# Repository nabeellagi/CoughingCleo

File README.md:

<div align="center">

# **COUGHING CLEO**

Poor air quality monitor.

*If air == bad -> cough!*

</div>

---

# SECTIONS

- [What is Coughing Cleo](#what-is-coughing-cleo)
    - [What are Cleo's expression?](#what-are-cleos-expression)
- [Why Cleo?](#why-cleo)
- [How to use it?](#how-to-use-it)
- [What Does This Repository Include?](#what-does-this-repository-include)
- [Footages](#footages)
    - [PCB and Schematics](#pcb-and-schematics)
        - [Custom ESP32-S3 Chip Based](#custom-esp32-s3-chip-based)
        - [XIAO ESP32-S3 Based](#xiao-esp32-s3-based)
    - [Enclosure and Assembly](#enclosure-and-assembly)
    - [Schematics](#schematics)
    - [Stickers](#stickers)
    - [Web Interface](#web-interface)
- [What softwares do I need?](#what-softwares-do-i-need)
- [BOM](#bom)
    - [Main BOM](#main-bom)
    - [Other BOMs](#other-boms)
---

## What is Coughing Cleo?

<div align="center">
    </img>
</div>

Coughing Cleo is an ESP32 based digital pet that detects the air quality using ENS160 sensor that will play a coughing noise if the sensor reads poor air quality.

Not only that, Cleo (the name of the cat, inside trapped inside the OLED) also show various of other expressions such as a bigger cough, sweating if the temperature is hot enough, and annoyed if the owner doesn't pet it.

### What are Cleo's expression?

Right now we have :

1. Small Cough
2. Big Cough
3. Sweating
4. Annoyed
5. Jolly when pet
6. IDLE

Also you can see Cleo and its companion at the back part of the bottom enclosure artwork!

Cleo is the black and white cat on the left side!

---

## Why Cleo?

Many pollutants have no smell or colors! That is why sometimes we didn't realize these pollutants were hurting us in different ways; they made us feel dizzy, headache, tired, and other long-term risks.

By having Coughing Cleo inside your room or any other place, you'd be able to hear its cough and then take an action regarding the poor air quality! Whether you move to another place, open a window, or take any other action, Cleo will be the one to remind you to do it!

My inspiration for this project was the Karhutla event in Indonesia, or Forest Fires. Although the sensor itself doesn't detect the particles from forest fires' smoke or solve the pollution issue directly, Coughing Cleo is made to raise the awareness of how important air quality is to a human being!

---

## Cleo's Coughing Condition

Based on the sensor readings, this is the table for Cleo's cough.

### **TVOC LEVEL**

| TVOC (PPB)  | Indication   | Cough             |
|-------------|--------------|-------------------|
| < 150       | Safe         | No Cough          |
| 150 - 500   | Acceptable   | Single Cough      |
| 500 - 1500  | Conspicuous  | Small Cough       |
| 1500 - 5000 | Concerning   | Big Cough         |
| > 5000      | Unacceptable | Big Cough, louder |

### **eCO₂**

| eCO₂        | Cough             |
|-------------|-------------------|
| 400 - 600   | No Cough          |
| 600 - 800   | No Cough          |
| 800 - 1000  | Small Cough       |
| 1000 - 1500 | Big Cough         |
| > 1500      | Big Cough, louder |

### **AQI-UBA**

| AQI-UBA | Cough             |
|---------|-------------------|
| 1       | No Cough          |
| 2       | No Cough          |
| 3       | Small Cough       |
| 4       | Big Cough         |
| 5       | Big Cough, louder |

---

## How to use it?

After you assembled the whole thing and flashed the firmware into the PCB as well as applied those cute stickers, here's how to use it.

1. Plug it into a power source using USB type C.
2. Whether you make it stand horizontally or vertically, make sure the backpart, specifically the sensor area, is exposed to the open space.
3. Plug in a speaker to the JST connection

Now Cleo the Cat will tell you if there's something wrong with your air!

Additionally, you can access the web interface to change the coughing sound or export the data logs.

---

## What Does This Repository Include?

In this repository you'll get :

1. The **PCB File** inside `PCB` folder which includes both PCB and Schematics
2. The **Enclosure File** inside `Enclosure` folder
3. The **Default Audio** Files inside `Default-Audio` folder
4. The **Artwork Files** inside `Stickers` folder which includes both the editable layout file  in form of Inkscape `.svg` and the art itself
5. The **Sprite Files** inside `Face-Sprite` folder
    - There's also face sprite code module test using Wokwi simulation that utilizes different sensor because of its limited feature located inside `Face-Sprite/wokwi-test`
6. The **Web Interface Files** inside  `Web-Interface` which has :
    - The UI design files
    - The Vite-Based + Solid.Js web user interface located inside `Web-Interface/esp32-web-interface`

---

## Footages
Take a look at Coughing Cleo!

### PCB and Schematics

There are two PCB and Schematics provided inside this repository

1. The Custom PCB : A customized PCB with bare ESP32 (ESP32-S3-WROOM-1U-N8R8) chip soldered directly
2. XIAO Based PCB Board : Custom PCB board that utilizes mini XIAO ESP32-S3 DIP solder.

| **Custom ESP32 WROOM chip based**                            | **Seeed Studio XIAO ESP32-S3 based**              |
|----------------------------------------------------------|-----------------------------------------------|
| Included on JLCPCB Standard PCBA Service                 | Solder it yourself                            |
| More expensive because it utilizes Standard PCBA service | Cheaper because it uses Economic PCBA service |
| 4 Layers with power pour                                 | 4 Layers without power pour                   |
| Gerber [Click here](PCB\Custom-PCB\production\PCB.zip)   | Gerber [Click here](PCB\XIAO-Based\production\PCB.zip)                |

Now here are the screenshots:

#### Custom ESP32-S3 Chip Based

The Schematic

The PCB

#### XIAO ESP32-S3 Based

The Schematic

The PCB

---

### Enclosure and Assembly

For the assembly itself you'll need

1. 3 pcs of M3x8 screws
2. A piece of M3x12 screw

Why the screw differences? As you can see on the image below, one hole has a higher level than the other. To make sure the screw to be able to bite the bottom part of the enclosure, we need a taller one!

After that you can put on the stickers and plug the speaker in using the JST connection.

### Stickers

### Web Interface

---

## What softwares do I need?

There are various of tools were used to design Coughing Cleo. Here are the tools that you might need to install to open the project files!

1. PCB ➜  Use [**KiCad**](https://www.kicad.org/download/) to open/edit schematics and PCB
2. Audio Files ➜ Use [**Audacity 4**](https://www.musehub.com/en-us/app/audacity) in order to open the audio file projects
3. Enclosure ➜ Use [**FreeCAD**](https://www.freecad.org/downloads.php?lang=en) to open/edit the enclosure model.
4. Face Sprite ➜  Use [**Aseprite**](https://aseprite.org/) or [**Resprite**](https://resprite.fengeon.com/) to open the .aseprite file to access Cleo The Cat faces
    - As for the face module test you can paste the project codes or import it to Wokwi or **[Here](https://wokwi.com/projects/479777241218679809)**
5. Sticker Artwork ➜ inside `ibis_files` folder you can found .ipv files, use [**Ibis Paint X**](https://ibispaint.com/?lang=en-US) to access the art work files
6. Sticker Print ➜ Feel free to print the PDF or you can change the layout using [**Inkscape**](https://inkscape.org/release/inkscape-1.4.2/windows/64-bit/msi/dl/)
7. Web Interface UI design ➜ Use [**Penpot**](https://penpot.app/) to open the web interface design
8. Web Interface Development ➜ In order to run the web interface locally for testing and development, you may use [Node.Js](https://nodejs.org/en)
    - After that change your directory into `cd Web-Interface/esp32-web-interface` and go ahead run `npm install` and to run it `npm run dev`
---

## BOM

### Main BOM

Even though there's the PCB BOMs, the actual full item BOM is located at
[`BOM/main.csv`](BOM/main.csv).
You can also read the [PDF version](BOM/main.pdf) or access the [XLSX version](BOM/main.xlsx)

### Other BOMs

1. JLCPCB and KiCad Fabrication tool generated
    - `BOM\Custom-PCB\bom-JLCPCB Assembly Order.xls`
    - `BOM\XIAO-Based\bom-JLCPCB Assembly Order.xls`

---

## Development Status 

The project is still in progress!

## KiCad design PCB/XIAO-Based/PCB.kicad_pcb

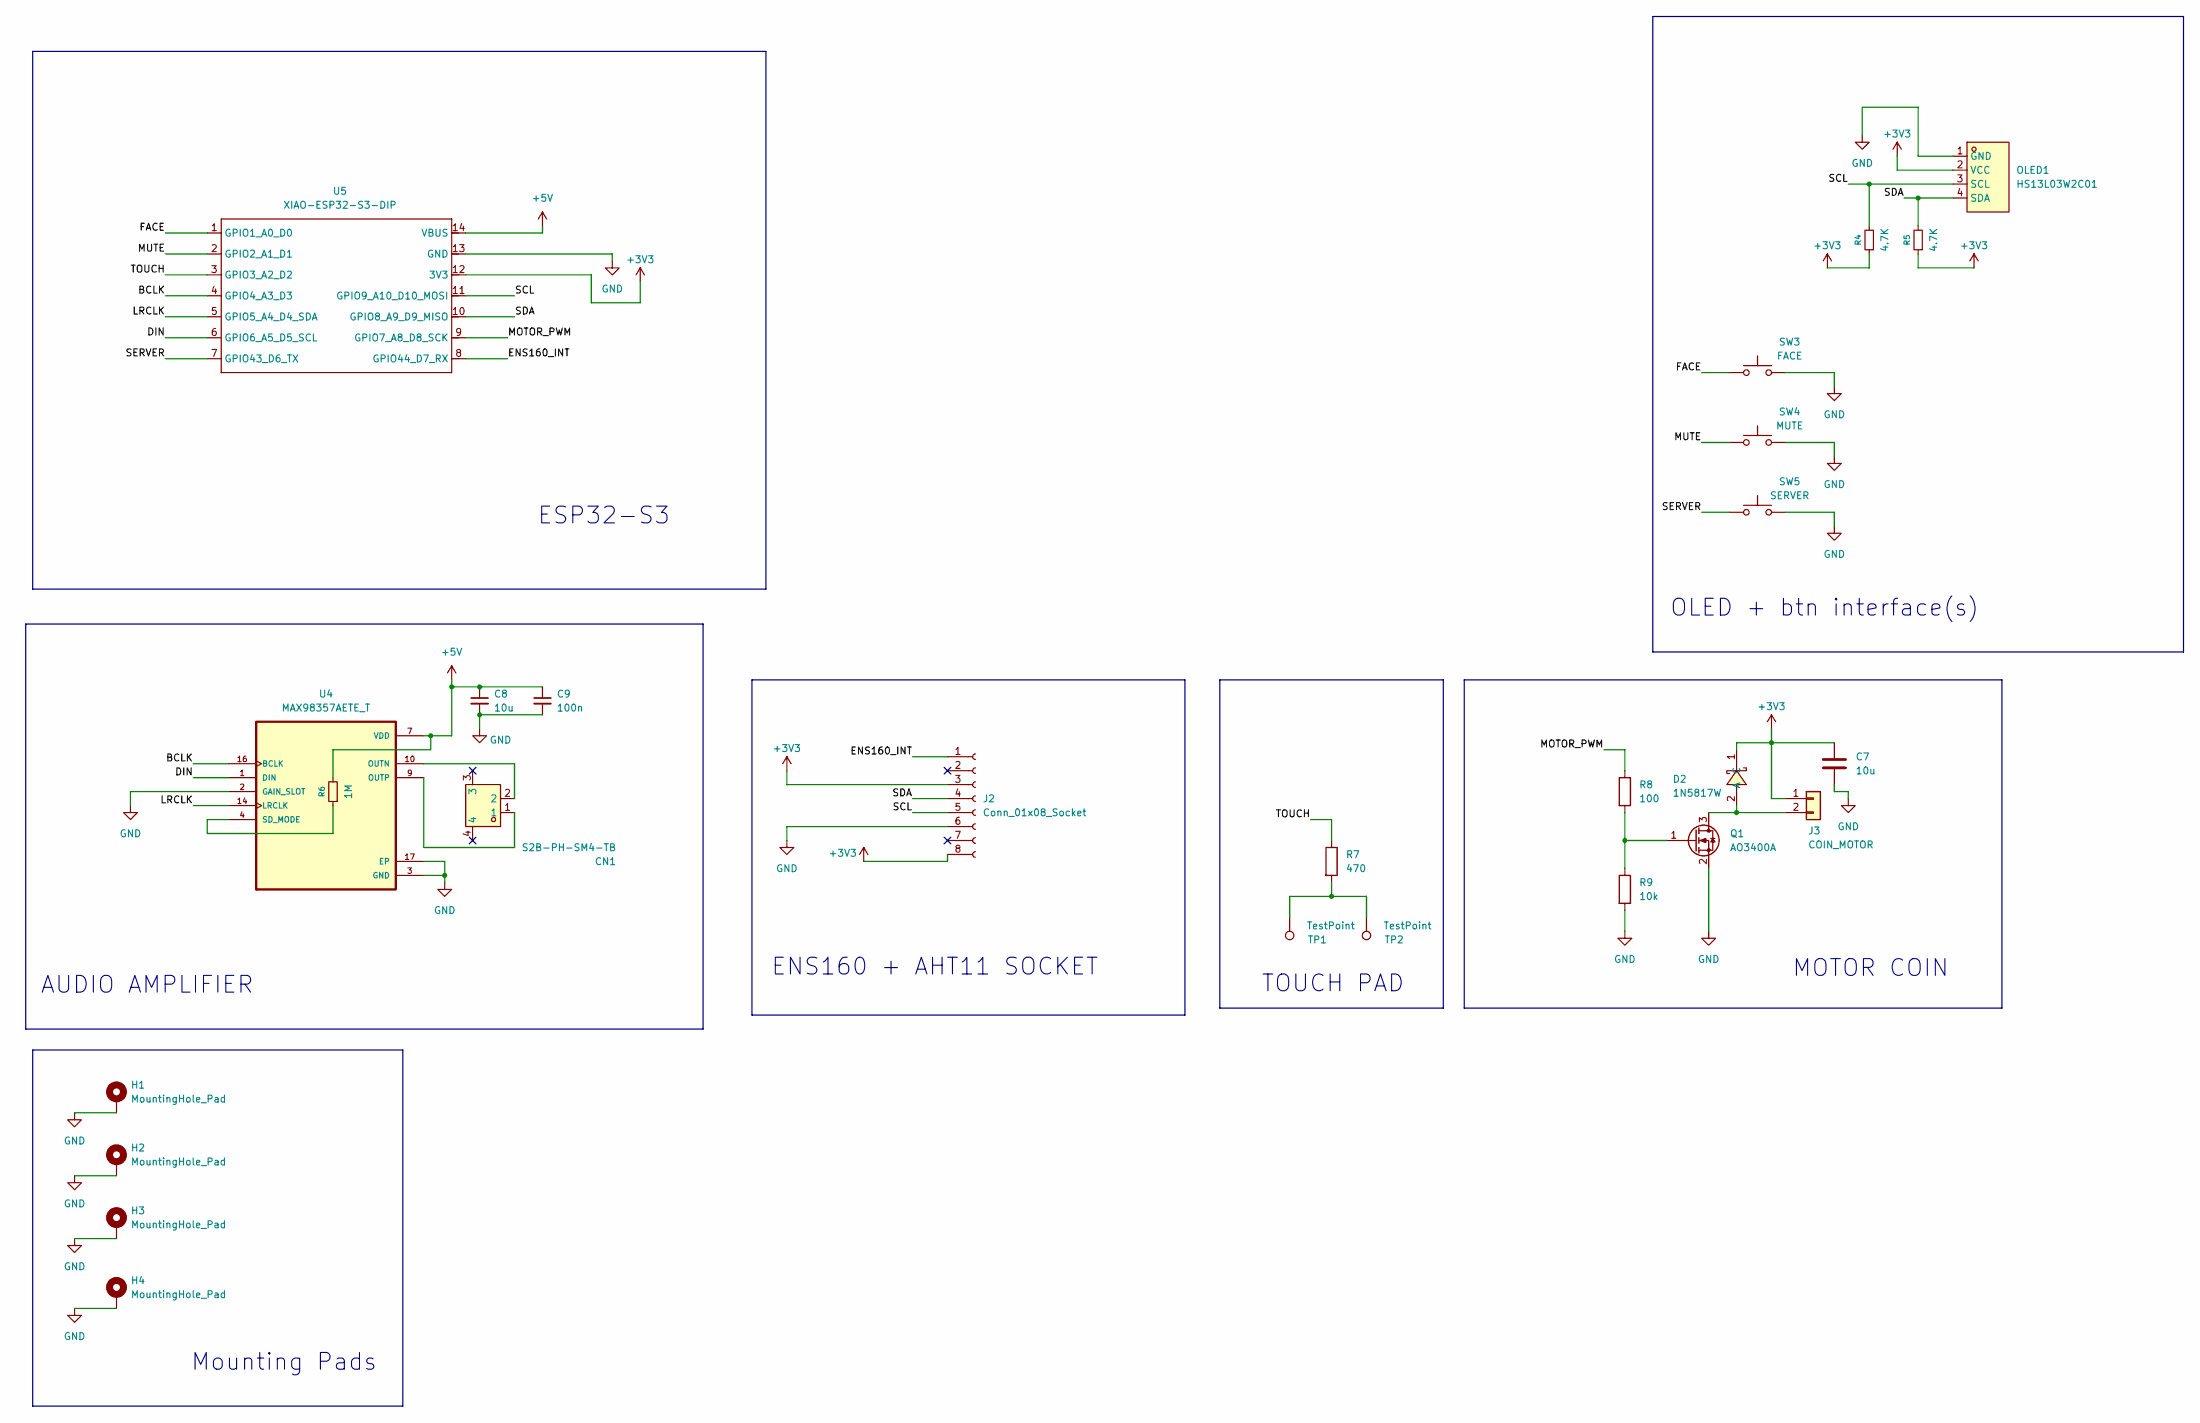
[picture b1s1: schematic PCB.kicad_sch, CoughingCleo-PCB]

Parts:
C7, C8: 10u; C_0805_2012Metric
C9: 100n; C_0603_1608Metric
CN1: S2B-PH-SM4-TB; CONN-SMD_P2.00_S2B-PH-SM4-TB-LF-SN; MPN S2B-PH-SM4-TB(LF)(SN); LCSC Part C295747
D2: 1N5817W; SOD-123_L2.8-W1.8-LS3.7-RD; MPN 1N5817W; LCSC Part C727113
H1, H2, H3, H4: MountingHole_Pad; MountingHole_3.2mm_M3_Pad
J2: Conn_01x08_Socket; PinHeader_1x08_P2.54mm_Vertical
J3: COIN_MOTOR; PinHeader_1x02_P2.54mm_Vertical
OLED1: HS13L03W2C01; OLED-TH_L35.4-W33.5_HS13L03W2C01; MPN HS13L03W2C01; LCSC Part C7465997
Q1: AO3400A; SOT-23
R4, R5: 4.7K; R_0603_1608Metric
R6: 1M; R_0603_1608Metric
R7: 470; R_0603_1608Metric
R8: 100; R_0603_1608Metric
R9: 10k; R_0603_1608Metric
SW3: FACE; SW_SPST_TL3342
SW4: MUTE; SW_SPST_TL3342
SW5: SERVER; SW_SPST_TL3342
TP1, TP2: TestPoint; TouchPad_D6mm
U4: MAX98357AETE_T; QFN50P300X300X80-17N
U5: XIAO-ESP32-S3-DIP

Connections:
+3V3: C7.1, D2.1 (C), J2.3, J2.8, J3.1, OLED1.2 (VCC), R4.1, R5.1, U5.12 (3V3)
+5V: C8.1, C9.1, R6.2, U4.7 (VDD), U4.8 (VDD), U5.14 (VBUS)
/BCLK: U4.16 (BCLK), U5.4 (GPIO4_A3_D3)
/DIN: U4.1 (DIN), U5.6 (GPIO6_A5_D5_SCL)
/ENS160_INT: J2.1, U5.8 (GPIO44_D7_RX)
/FACE: SW3.1, U5.1 (GPIO1_A0_D0)
/LRCLK: U4.14 (LRCLK), U5.5 (GPIO5_A4_D4_SDA)
/MOTOR_PWM: R8.1, U5.9 (GPIO7_A8_D8_SCK)
/MUTE: SW4.1, U5.2 (GPIO2_A1_D1)
/SCL: J2.5, OLED1.3 (SCL), R4.2, U5.11 (GPIO9_A10_D10_MOSI)
/SDA: J2.4, OLED1.4 (SDA), R5.2, U5.10 (GPIO8_A9_D9_MISO)
/SERVER: SW5.1, U5.7 (GPIO43_D6_TX)
/TOUCH: R7.1, U5.3 (GPIO3_A2_D2)
GND: C7.2, C8.2, C9.2, H1.1, H2.1, H3.1, H4.1, J2.6, OLED1.1 (GND), Q1.2 (S), R9.2, SW3.2, SW4.2, SW5.2, U4.2 (GAIN_SLOT), U4.3 (GND), U4.11 (GND), U4.15 (GND), U4.17 (EP), U5.13 (GND)
unnamed: D2.2 (A), J3.2, Q1.3 (D)
unnamed: Q1.1 (G), R8.2, R9.1
unnamed: R7.2, TP1.1, TP2.1
unnamed: CN1.2, U4.10 (OUTN)
unnamed: CN1.1, U4.9 (OUTP)
unnamed: R6.1, U4.4 (SD_MODE)

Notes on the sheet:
OLED + btn interface(s)
TOUCH PAD
AUDIO AMPLIFIER
ENS160 + AHT11 SOCKET
MOTOR COIN
Mounting Pads
ESP32-S3

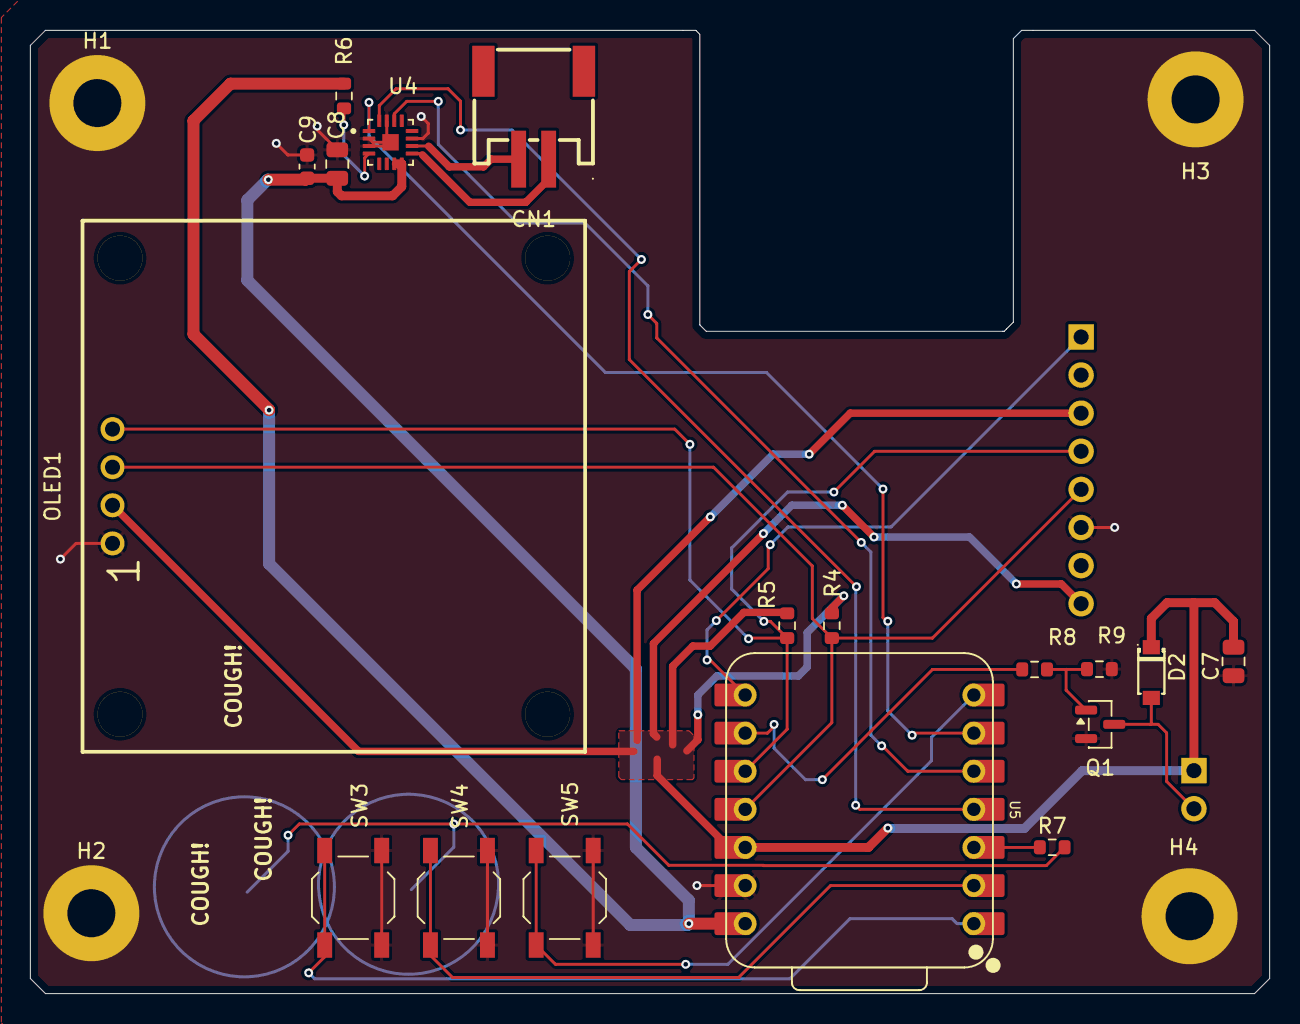
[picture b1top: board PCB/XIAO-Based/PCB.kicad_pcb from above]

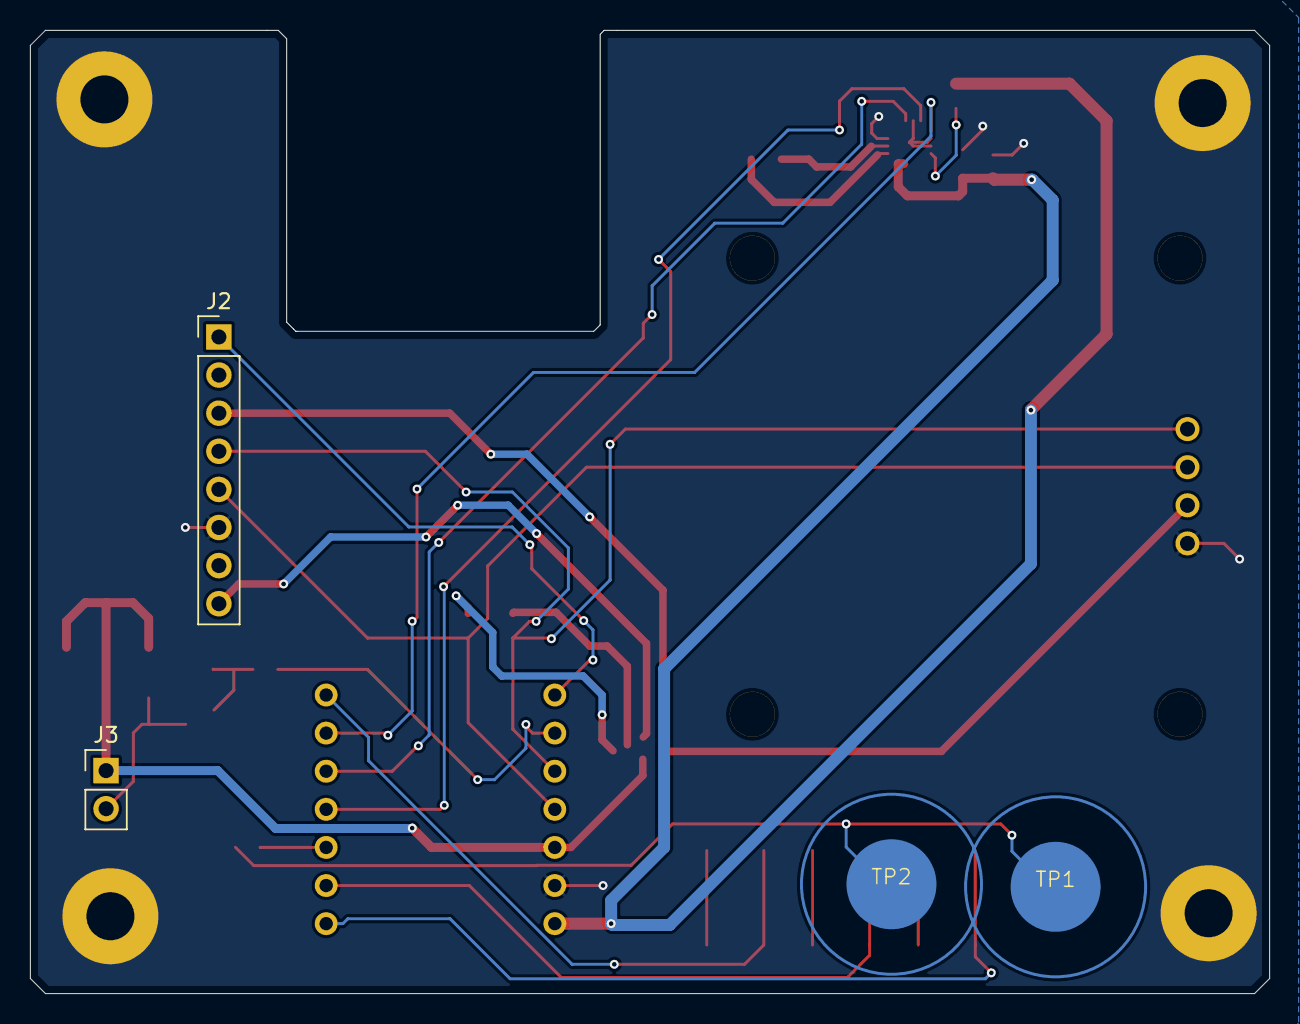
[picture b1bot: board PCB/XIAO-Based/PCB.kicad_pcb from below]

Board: 4 copper layers, 82.6 x 64.2 mm, 26 parts (4 on the bottom side), 20 nets.

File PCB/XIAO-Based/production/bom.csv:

Designator,Footprint,Quantity,Value,LCSC Part #
"C7, C8",0805,2,10u,
C9,0603,1,100n,
CN1,CONN-SMD_P2.00_S2B-PH-SM4-TB-LF-SN,1,S2B-PH-SM4-TB,C295747
D2,SOD-123_L2.8-W1.8-LS3.7-RD,1,1N5817W,C727113
Q1,SOT-23,1,AO3400A,
"R4, R5",0603,2,4.7K,
R6,0603,1,1M,
R7,0603,1,470,
R8,0603,1,100,
R9,0603,1,10k,
SW3,SW_SPST_TL3342,1,FACE,
SW4,SW_SPST_TL3342,1,MUTE,
SW5,SW_SPST_TL3342,1,SERVER,
U4,QFN50P300X300X80-17N,1,MAX98357AETE_T,

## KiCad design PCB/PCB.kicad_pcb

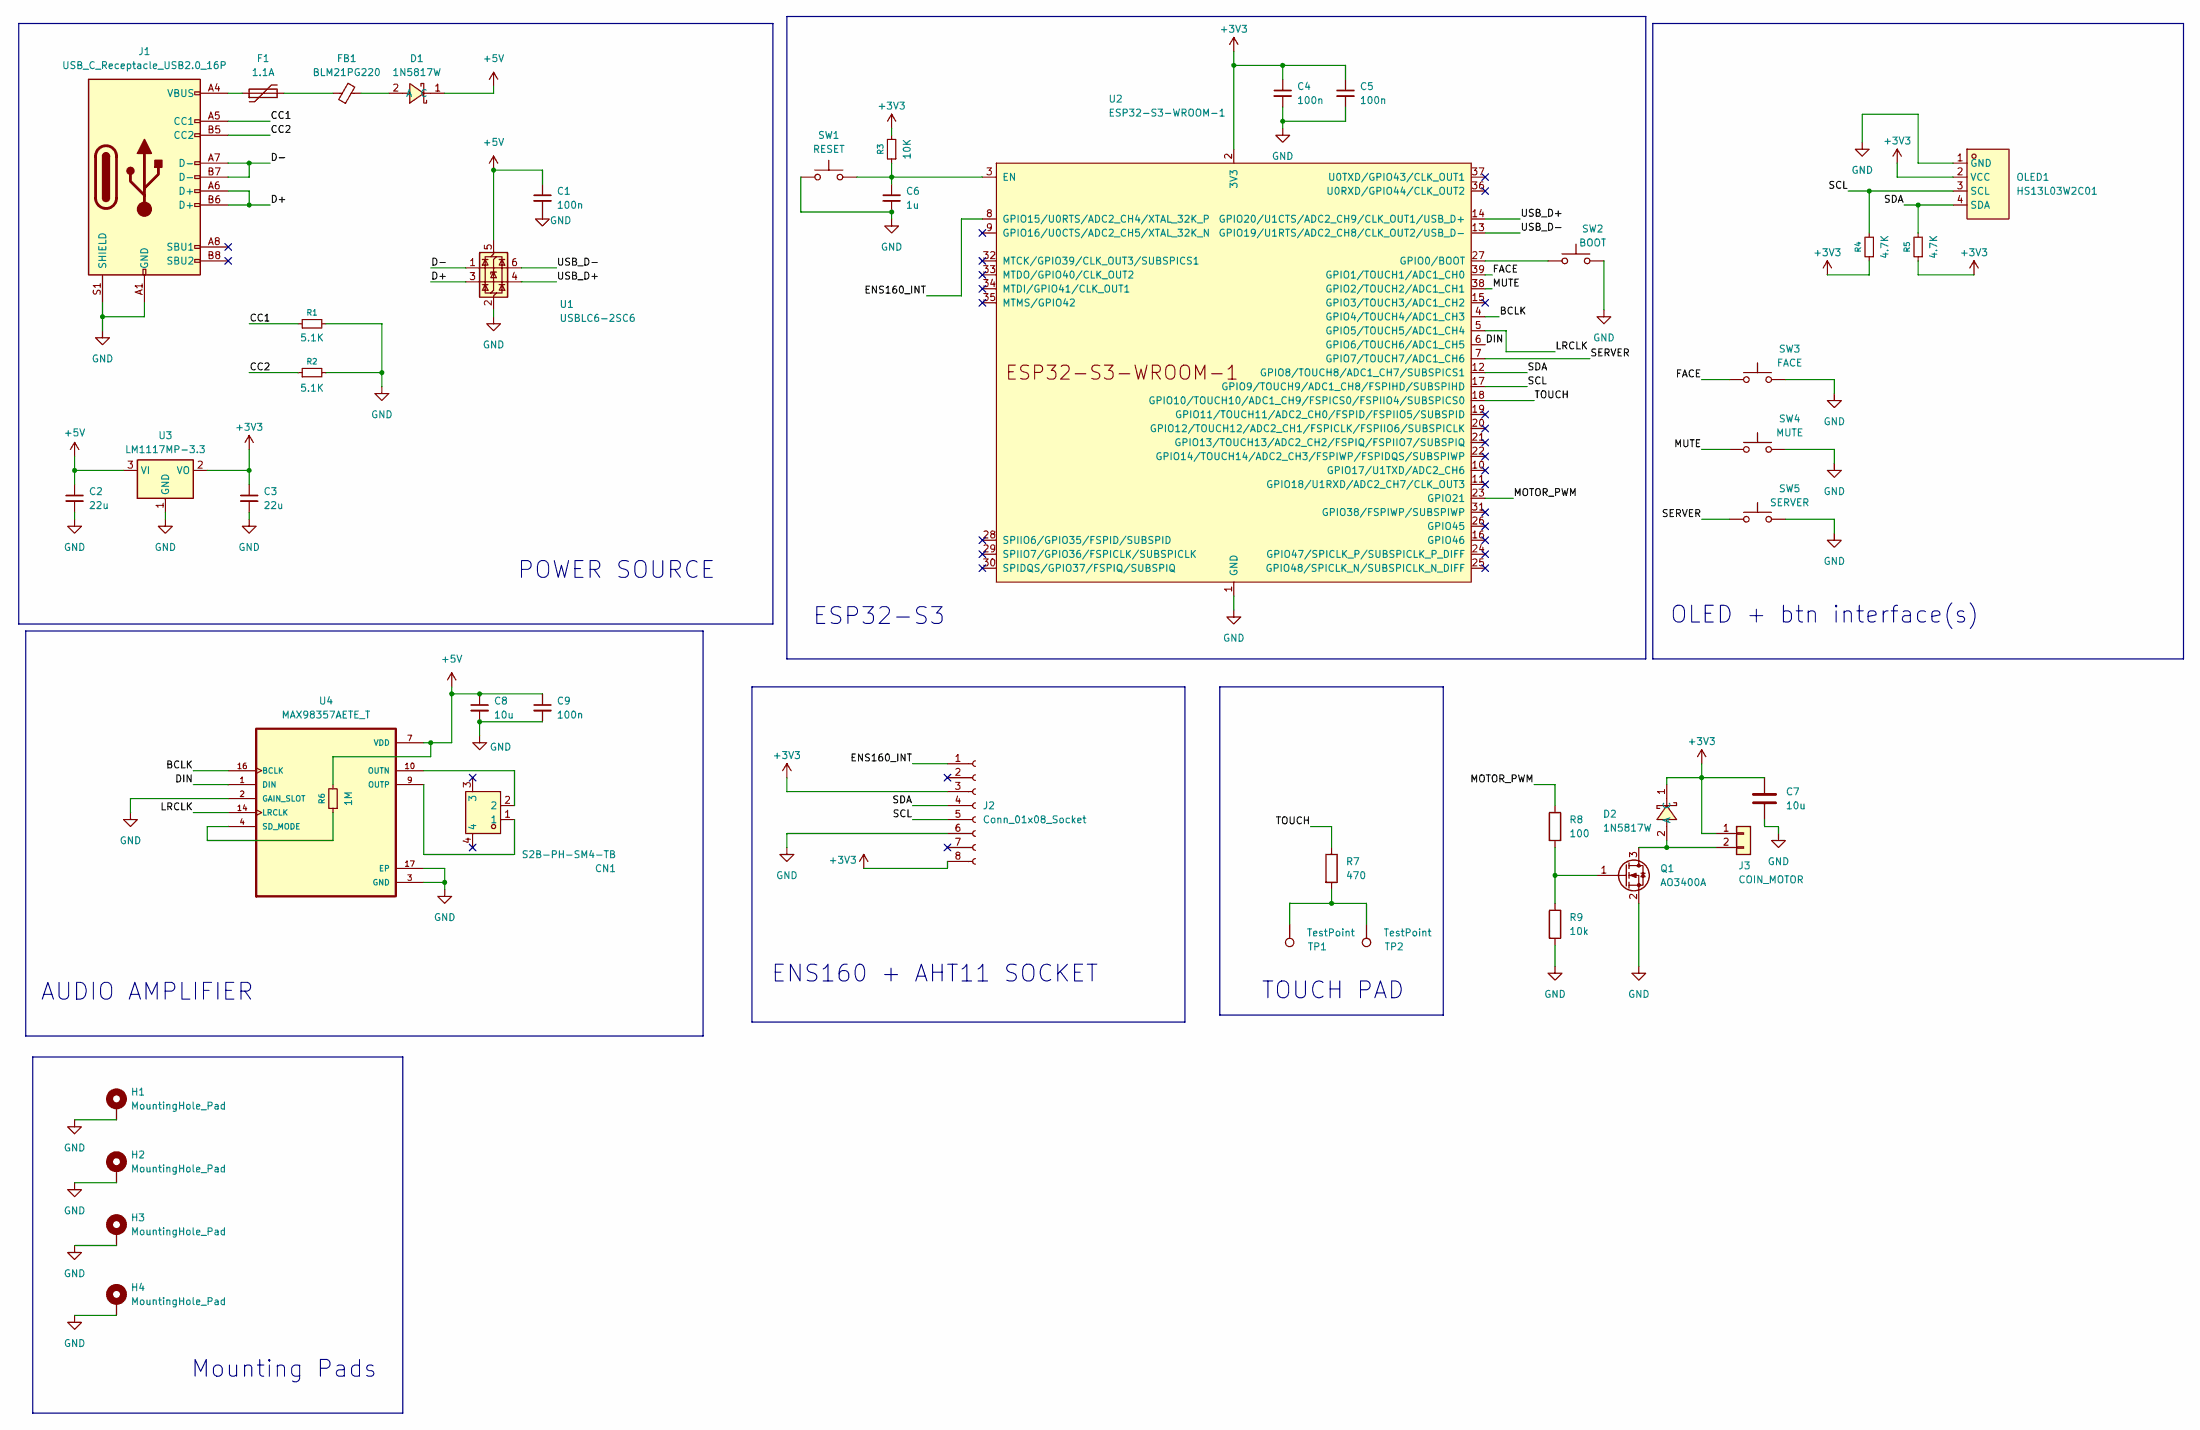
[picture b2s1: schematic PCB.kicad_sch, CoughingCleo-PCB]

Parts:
C1, C4, C5, C9: 100n; C_0603_1608Metric
C2, C3: 22u; C_0805_2012Metric
C6: 1u; C_0603_1608Metric
C7, C8: 10u; C_0805_2012Metric
CN1: S2B-PH-SM4-TB; CONN-SMD_P2.00_S2B-PH-SM4-TB-LF-SN; MPN S2B-PH-SM4-TB(LF)(SN); LCSC Part C295747
D1, D2: 1N5817W; SOD-123_L2.8-W1.8-LS3.7-RD; MPN 1N5817W; LCSC Part C727113
F1: 1.1A; Fuse_1206_3216Metric
FB1: BLM21PG220; L_0805_2012Metric
H1, H2, H3, H4: MountingHole_Pad; MountingHole_3.2mm_M3_Pad
J1: USB_C_Receptacle_USB2.0_16P; USB_C_Receptacle_HRO_TYPE-C-31-M-12
J2: Conn_01x08_Socket; PinHeader_1x08_P2.54mm_Vertical
J3: COIN_MOTOR; PinHeader_1x02_P2.54mm_Vertical
OLED1: HS13L03W2C01; OLED-TH_L35.4-W33.5_HS13L03W2C01; MPN HS13L03W2C01; LCSC Part C7465997
Q1: AO3400A; SOT-23
R1, R2: 5.1K; R_0603_1608Metric
R3: 10K; R_0603_1608Metric
R4, R5: 4.7K; R_0603_1608Metric
R6: 1M; R_0603_1608Metric
R7: 470; R_0603_1608Metric
R8: 100; R_0603_1608Metric
R9: 10k; R_0603_1608Metric
SW1: RESET; SW_SPST_B3U-1000P
SW2: BOOT; SW_SPST_B3U-1000P
SW3: FACE; SW_SPST_TL3342
SW4: MUTE; SW_SPST_TL3342
SW5: SERVER; SW_SPST_TL3342
TP1, TP2: TestPoint; TouchPad_D6mm
U1: USBLC6-2SC6; SOT-23-6
U2: ESP32-S3-WROOM-1
U3: LM1117MP-3.3; SOT-223-3_TabPin2
U4: MAX98357AETE_T; QFN50P300X300X80-17N

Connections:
+3V3: C3.1, C4.1, C5.1, C7.1, D2.1 (C), J2.3, J2.8, J3.1, OLED1.2 (VCC), R3.2, R4.1, R5.1, U2.2 (3V3), U3.2 (VO)
+5V: C1.1, C2.1, C8.1, C9.1, D1.1 (C), R6.2, U1.5 (VBUS), U3.3 (VI), U4.7 (VDD), U4.8 (VDD)
/BCLK: U2.4 (GPIO4/TOUCH4/ADC1_CH3), U4.16 (BCLK)
/CC1: J1.A5 (CC1), R1.1
/CC2: J1.B5 (CC2), R2.1
/D+: J1.A6 (D+), J1.B6 (D+), U1.3 (I/O2)
/D-: J1.A7 (D-), J1.B7 (D-), U1.1 (I/O1)
/DIN: U2.6 (GPIO6/TOUCH6/ADC1_CH5), U4.1 (DIN)
/ENS160_INT: J2.1, U2.8 (GPIO15/U0RTS/ADC2_CH4/XTAL_32K_P)
/FACE: SW3.1, U2.39 (GPIO1/TOUCH1/ADC1_CH0)
/LRCLK: U2.5 (GPIO5/TOUCH5/ADC1_CH4), U4.14 (LRCLK)
/MOTOR_PWM: R8.1, U2.23 (GPIO21)
/MUTE: SW4.1, U2.38 (GPIO2/TOUCH2/ADC1_CH1)
/SCL: J2.5, OLED1.3 (SCL), R4.2, U2.17 (GPIO9/TOUCH9/ADC1_CH8/FSPIHD/SUBSPIHD)
/SDA: J2.4, OLED1.4 (SDA), R5.2, U2.12 (GPIO8/TOUCH8/ADC1_CH7/SUBSPICS1)
/SERVER: SW5.1, U2.7 (GPIO7/TOUCH7/ADC1_CH6)
/TOUCH: R7.1, U2.18 (GPIO10/TOUCH10/ADC1_CH9/FSPICS0/FSPIIO4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)
/USB_D+: U1.4 (I/O2), U2.14 (GPIO20/U1CTS/ADC2_CH9/CLK_OUT1/USB_D+)
/USB_D-: U1.6 (I/O1), U2.13 (GPIO19/U1RTS/ADC2_CH8/CLK_OUT2/USB_D-)
GND: C1.2, C2.2, C3.2, C4.2, C5.2, C6.2, C7.2, C8.2, C9.2, H1.1, H2.1, H3.1, H4.1, J1.A1 (GND), J1.A12 (GND), J1.B1 (GND), J1.B12 (GND), J1.S1 (SHIELD), J2.6, OLED1.1 (GND), Q1.2 (S), R1.2, R2.2, R9.2, SW1.1, SW2.2, SW3.2, SW4.2, SW5.2, U1.2 (GND), U2.1 (GND), U2.40 (GND), U2.41 (GND), U3.1 (GND), U4.2 (GAIN_SLOT), U4.3 (GND), U4.11 (GND), U4.15 (GND), U4.17 (EP); also elsewhere on the board
unnamed: D1.2 (A), FB1.2
unnamed: D2.2 (A), J3.2, Q1.3 (D)
unnamed: F1.1, J1.A4 (VBUS), J1.A9 (VBUS), J1.B4 (VBUS), J1.B9 (VBUS)
unnamed: F1.2, FB1.1
unnamed: Q1.1 (G), R8.2, R9.1
unnamed: R7.2, TP1.1, TP2.1
unnamed 26: C6.1, R3.1, SW1.2, U2.3 (EN); also elsewhere on the board
unnamed 27: SW2.1, U2.27 (GPIO0/BOOT); also elsewhere on the board
unnamed: CN1.2, U4.10 (OUTN)
unnamed: CN1.1, U4.9 (OUTP)
unnamed: R6.1, U4.4 (SD_MODE)

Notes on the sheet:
OLED + btn interface(s)
TOUCH PAD
AUDIO AMPLIFIER
ENS160 + AHT11 SOCKET
Mounting Pads
ESP32-S3
POWER SOURCE

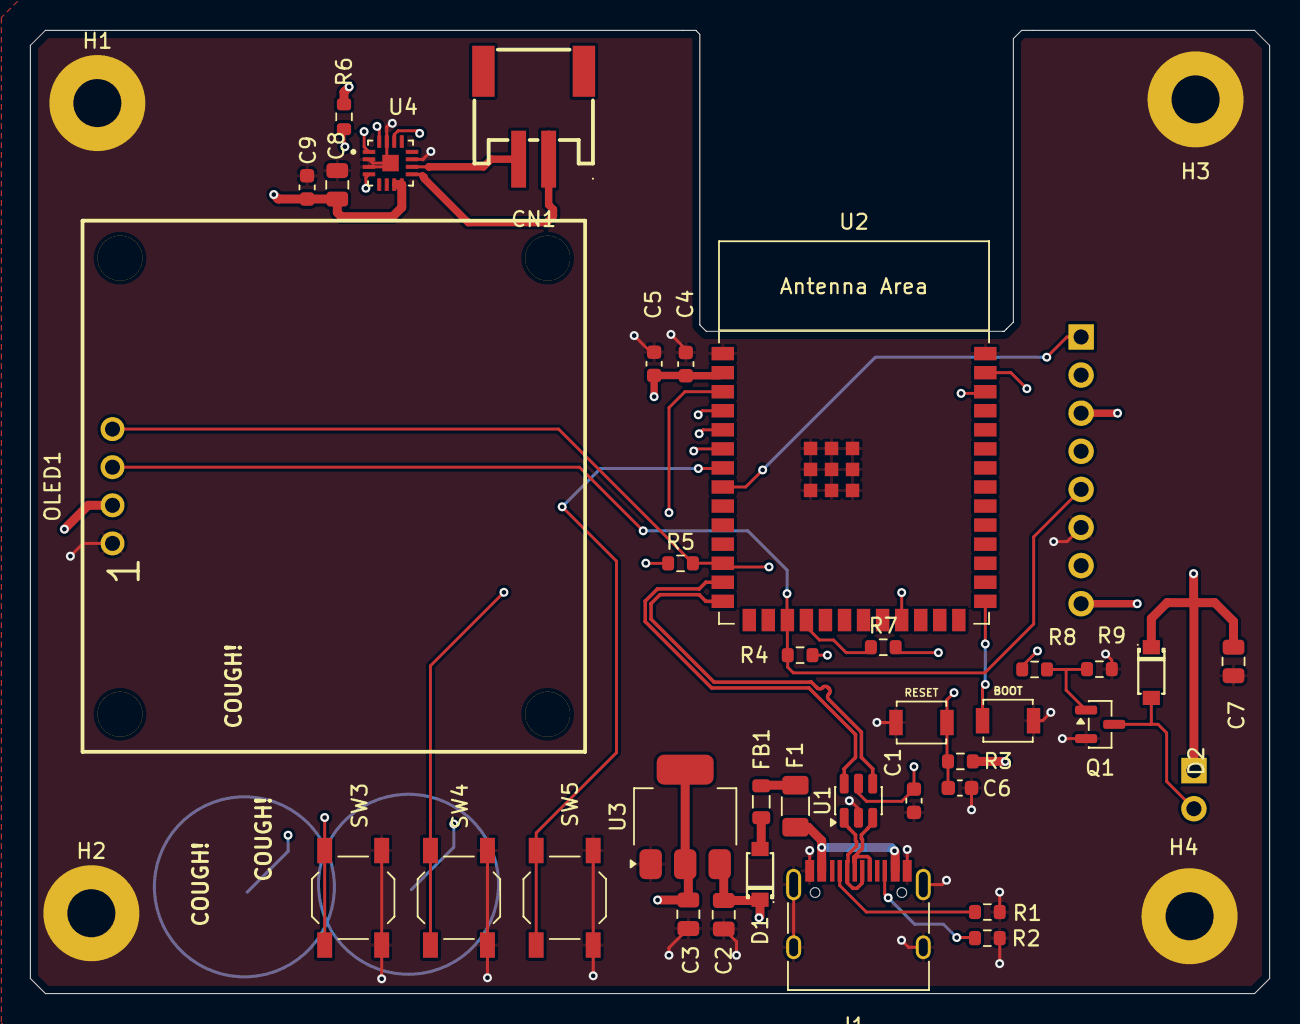
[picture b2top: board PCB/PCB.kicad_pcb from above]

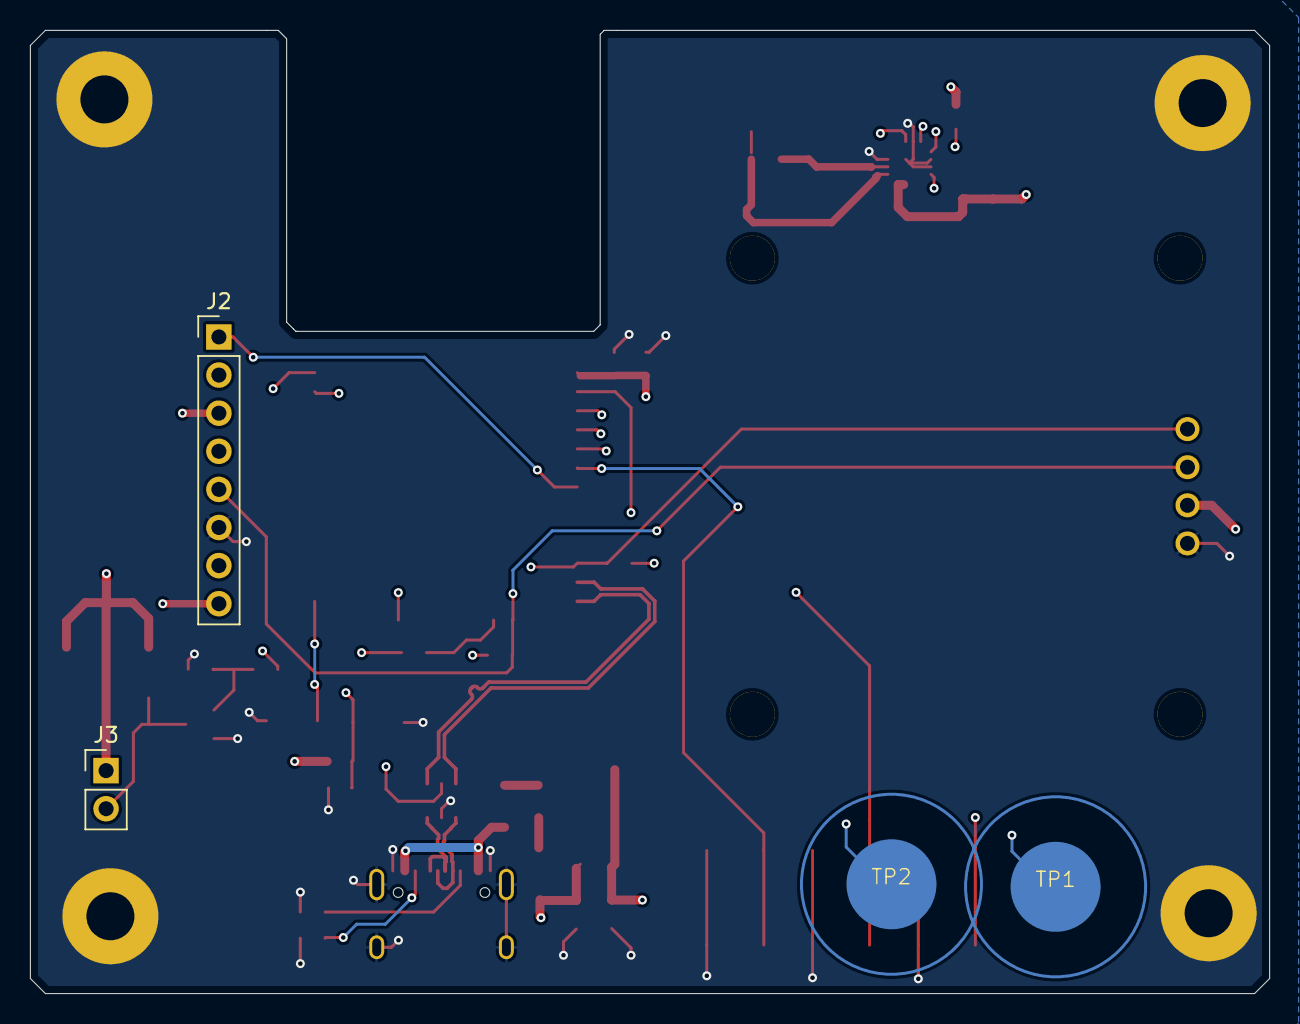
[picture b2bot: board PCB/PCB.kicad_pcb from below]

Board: 4 copper layers, 82.6 x 64.2 mm, 43 parts (4 on the bottom side), 31 nets.

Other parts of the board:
BOOT: BOOT; SW_SPST_B3U-1000P
RESET: RESET; SW_SPST_B3U-1000P

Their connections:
GND: BOOT.2, RESET.1; also elsewhere on the board
unnamed 26: RESET.2; also elsewhere on the board
unnamed 27: BOOT.1; also elsewhere on the board

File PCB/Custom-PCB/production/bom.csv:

Designator,Footprint,Quantity,Value,LCSC Part #
BOOT,SW_SPST_B3U-1000P,1,BOOT,
"C1, C4, C5, C9",0603,4,100n,
"C2, C3",0805,2,22u,
C6,0603,1,1u,
"C7, C8",0805,2,10u,
CN1,CONN-SMD_P2.00_S2B-PH-SM4-TB-LF-SN,1,S2B-PH-SM4-TB,C295747
"D1, D2",SOD-123_L2.8-W1.8-LS3.7-RD,2,1N5817W,C727113
F1,1206,1,1.1A,
FB1,0805,1,BLM21PG220,
J1,USB_C_Receptacle_HRO_TYPE-C-31-M-12,1,USB_C_Receptacle_USB2.0_16P,
J2,PinHeader_1x08_P2.54mm_Vertical,1,Conn_01x08_Socket,
J3,PinHeader_1x02_P2.54mm_Vertical,1,COIN_MOTOR,
OLED1,OLED-TH_L35.4-W33.5_HS13L03W2C01,1,HS13L03W2C01,C7465997
Q1,SOT-23,1,AO3400A,
"R1, R2",0603,2,5.1K,
"R3, R9",0603,2,10K,
"R4, R5",0603,2,4.7K,
R6,0603,1,1M,
R7,0603,1,470,
R8,0603,1,100,
RESET,SW_SPST_B3U-1000P,1,RESET,
SW3,SW_SPST_TL3342,1,FACE,
SW4,SW_SPST_TL3342,1,MUTE,
SW5,SW_SPST_TL3342,1,SERVER,
U1,SOT-23-6,1,USBLC6-2SC6,
U2,ESP32-S3-WROOM-1,1,ESP32-S3-WROOM-1,
U3,SOT-223-3_TabPin2,1,LM1117MP-3.3,
U4,QFN50P300X300X80-17N,1,MAX98357AETE_T,
